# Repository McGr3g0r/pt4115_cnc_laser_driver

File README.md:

# pt4115_cnc_laser_driver

This is simple PT4115 IC diode driver for CNC Laser.

My laser is Nichia 1.8W module. The current is set for 0.9A

The PCB has been engraved using V-bit on the same 3018 CNC machine

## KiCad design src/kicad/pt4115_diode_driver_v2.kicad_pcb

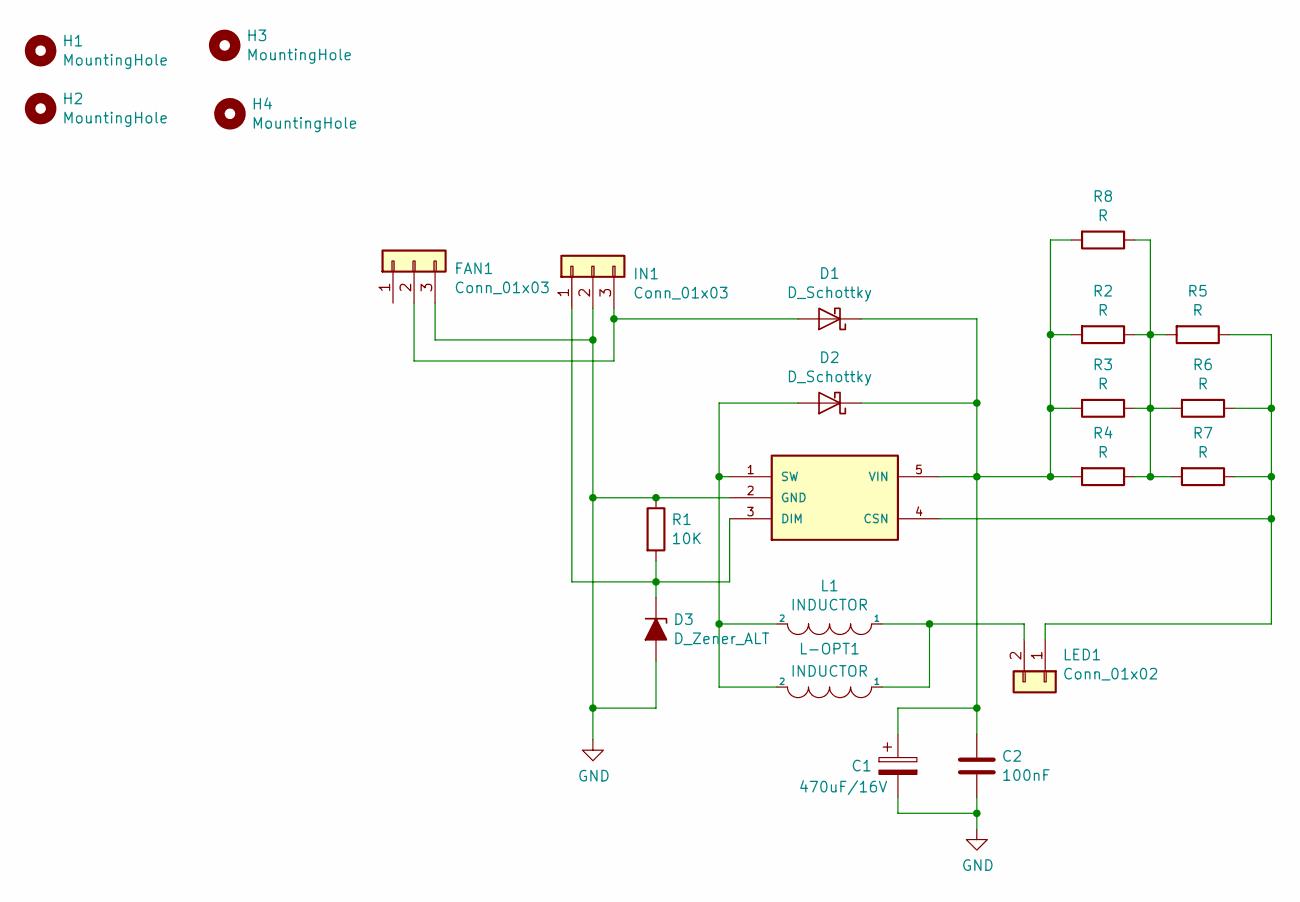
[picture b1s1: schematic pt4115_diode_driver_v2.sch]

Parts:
C1: 470uF/16V; CP_Elec_10x7.7
C2: 100nF; C_0805_2012Metric
D1, D2: D_Schottky; D_SMC
D3: D_Zener_ALT; D_SOD-123
FAN1: Conn_01x03; PinHeader_1x03_P2.54mm_Horizontal
H1, H2, H3, H4: MountingHole; MountingHole_3.2mm_M3_Pad
IN1: Conn_01x03; PinHeader_1x03_P2.54mm_Horizontal
L1: INDUCTOR; L_Radial_D10.0mm_P5.00mm_Fastron_07M
L-OPT1: INDUCTOR; L_Wuerth_WE-PDF
LED1: Conn_01x02; PinHeader_1x02_P2.54mm_Horizontal
R1: 10K; R_0805_2012Metric
R2, R3, R4, R5, R6, R7: R; R_0805_2012Metric
R8: R; R_1206_3216Metric
U1: PT4115; SOT-89-5

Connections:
GND: C1.2, C2.2, D3.2 (A), FAN1.3, IN1.2, R1.1, U1.2 (GND)
unnamed: C1.1, C2.1, D1.1 (K), D2.1 (K), R2.2, R3.2, R4.2, R8.2, U1.5 (VIN)
unnamed: D1.2 (A), FAN1.2, IN1.3
unnamed: D2.2 (A), L1.2, L-OPT1.2, U1.1 (SW)
unnamed: D3.1 (K), IN1.1, R1.2, U1.3 (DIM)
unnamed: L1.1, L-OPT1.1, LED1.2
unnamed: LED1.1, R5.1, R6.1, R7.1, U1.4 (CSN)
unnamed: R2.1, R3.1, R4.1, R5.2, R6.2, R7.2, R8.1

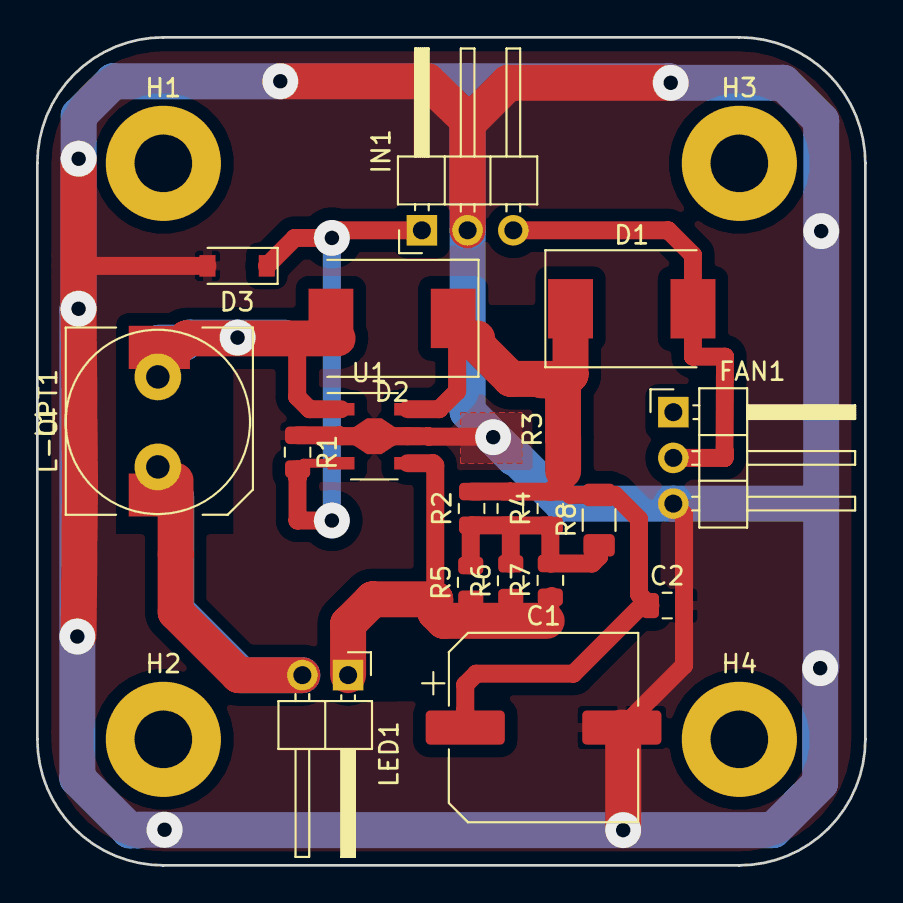
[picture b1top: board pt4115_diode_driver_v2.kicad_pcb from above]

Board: 2 copper layers, 46.0 x 46.0 mm, 23 parts (0 on the bottom side), 8 nets.

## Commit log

2022-04-21 initial kicad project commit
2022-04-21 images and readme updated
